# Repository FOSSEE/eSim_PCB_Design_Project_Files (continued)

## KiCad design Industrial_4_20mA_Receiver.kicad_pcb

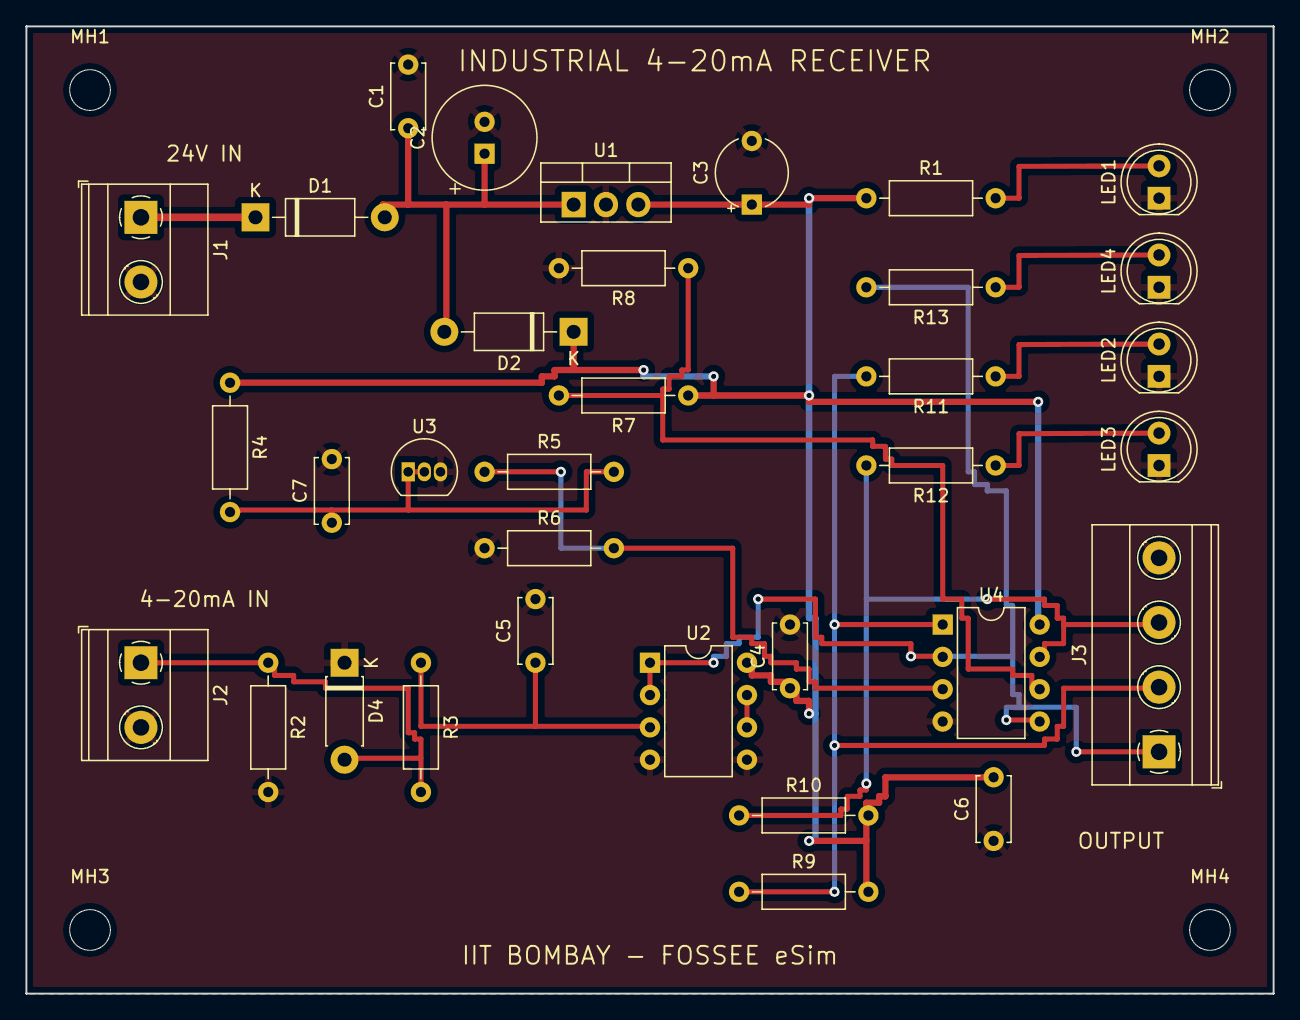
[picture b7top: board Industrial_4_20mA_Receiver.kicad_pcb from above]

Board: 2 copper layers, 98.0 x 76.0 mm, 38 parts (0 on the bottom side), 17 nets.

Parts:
C1, C4, C5, C6, C7: 100nF; C_Disc_D5.0mm_W2.5mm_P5.00mm
C2: 100uF; CP_Radial_Tantal_D8.0mm_P2.50mm
C3: 10uF; CP_Radial_Tantal_D5.5mm_P5.00mm
D1, D2: 1N4007; D_DO-41_SOD81_P10.16mm_Horizontal
D4: 5.6V; D_DO-41_SOD81_P7.62mm_Horizontal
J1: 24v_IN; TerminalBlock_Phoenix_MKDS-1,5-2-5.08_1x02_P5.08mm_Horizont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
J2: SENSOR_IN; TerminalBlock_Phoenix_MKDS-1,5-2-5.08_1x02_P5.08mm_Horizont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
J3: OUTPUT; TerminalBlock_Phoenix_MKDS-1,5-4-5.08_1x04_P5.08mm_Horizont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
LED1: Blue; LED_D5.0mm_Clear
LED2: Yellow; LED_D5.0mm_Clear
LED3: Red; LED_D5.0mm_Clear
LED4: Green; LED_D5.0mm_Clear
MH1, MH2, MH3, MH4: MountingHole_3.2mm_M3
R1: 2.2k; R_Axial_DIN0207_L6.3mm_D2.5mm_P10.16mm_Horizontal
R2: 250; R_Axial_DIN0207_L6.3mm_D2.5mm_P10.16mm_Horizontal
R3: 1K; R_Axial_DIN0207_L6.3mm_D2.5mm_P10.16mm_Horizontal
R4: 3.3K; R_Axial_DIN0207_L6.3mm_D2.5mm_P10.16mm_Horizontal
R5: 10k; R_Axial_DIN0207_L6.3mm_D2.5mm_P10.16mm_Horizontal
R6, R9, R10: 4.7K; R_Axial_DIN0207_L6.3mm_D2.5mm_P10.16mm_Horizontal
R7: 6.8k; R_Axial_DIN0207_L6.3mm_D2.5mm_P10.16mm_Horizontal
R8: 5.1K; R_Axial_DIN0207_L6.3mm_D2.5mm_P10.16mm_Horizontal
R11, R12, R13: 2.2K; R_Axial_DIN0207_L6.3mm_D2.5mm_P10.16mm_Horizontal
U1: LM7812_TO220; TO-220-3_Vertical
U2: LM358; DIP-8_W7.62mm
U3: TL431LP; TO-92_Inline
U4: LM393; DIP-8_W7.62mm

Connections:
+12V: C3.1 (A), C4.1 (A), C6.2 (B), D2.1 (+), R1.1, R4.1, R7.1, R9.2, R10.2, U1.3 (VO), U2.8 (V+), U4.8 (V+)
GND: C1.2 (B), C2.2 (B), C3.2 (B), C4.2 (B), C5.2 (B), C6.1 (A), C7.2 (B), D4.1 (+), J1.2, J2.2, J3.4, LED1.1 (K), LED2.1 (K), LED3.1 (K), LED4.1 (K), R2.2, R6.1, R8.2, U1.2 (GND), U2.4 (V-), U2.5, U3.3 (K), U4.4 (V-)
unnamed: C5.1 (A), R3.1, U2.3 (+)
unnamed: D1.1 (+), J1.1
unnamed: C1.1 (A), C2.1 (A), D1.2 (-), D2.2 (-), U1.1 (VI)
unnamed: LED2.2 (A), R11.1
unnamed: LED4.2 (A), R13.1
unnamed: LED1.2 (A), R1.2
unnamed: D4.2 (-), J2.1, R2.1, R3.2
unnamed: J3.2, R9.1, R11.2, U4.1
unnamed: LED3.2 (A), R12.1
unnamed: U2.6, U2.7
unnamed: C7.1 (A), R4.2, R5.2, U3.1 (REF), U3.2 (A)
unnamed: J3.3, R10.1, R12.2, U4.7
V_BUFFERED: J3.1, R13.2, U2.1, U2.2 (-), U4.2 (-), U4.5 (+)
V_REF_HIGH: R7.2, R8.1, U4.6 (-)
V_REF_LOW: R5.1, R6.2, U4.3 (+)
